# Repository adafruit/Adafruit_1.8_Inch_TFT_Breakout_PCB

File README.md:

# 1.8" Color TFT LCD display with MicroSD Card Breakout

<a href="http://www.adafruit.com/products/358"><br/>Click here to purchase one from the Adafruit shop</a>

This lovely little display breakout is the best way to add a small, colorful and bright display to any project. Since the display uses 4-wire SPI to communicate and has its own pixel-addressable frame buffer, it can be used with every kind of microcontroller. Even a very small one with low memory and few pins available!

The 1.8" display has 128x160 color pixels. Unlike the low cost "Nokia 6110" and similar LCD displays, which are CSTN type and thus have poor color and slow refresh, this display is a true TFT! The TFT driver (ST7735R) can display full 18-bit color (262,144 shades!). And the LCD will always come with the same driver chip so there's no worries that your code will not work from one to the other.

The breakout has the TFT display soldered on (it uses a delicate flex-circuit connector) as well as a ultra-low-dropout 3.3V regulator and a 3/5V level shifter so you can use it with 3.3V or 5V power and logic. We also had a little space so we placed a microSD card holder so you can easily load full color bitmaps from a FAT16/FAT32 formatted microSD card. The microSD card is not included, [but you can pick one up here](https://www.adafruit.com/product/102).

Of course, we wouldn't just leave you with a datasheet and a "good luck!" - [we've written a full open source graphics library that can draw pixels, lines, rectangles, circles, text and bitmaps as well as example code and a wiring tutorial](https://learn.adafruit.com/1-8-tft-display). The code is written for Arduino but can be easily ported to your favorite microcontroller!

### License

Adafruit invests time and resources providing this open source design, please support Adafruit and open-source hardware by purchasing products from [Adafruit](https://www.adafruit.com)!

Designed by Limor Fried/Ladyada for Adafruit Industries.

Creative Commons Attribution/Share-Alike, all text above must be included in any redistribution. See license.txt for additional details.

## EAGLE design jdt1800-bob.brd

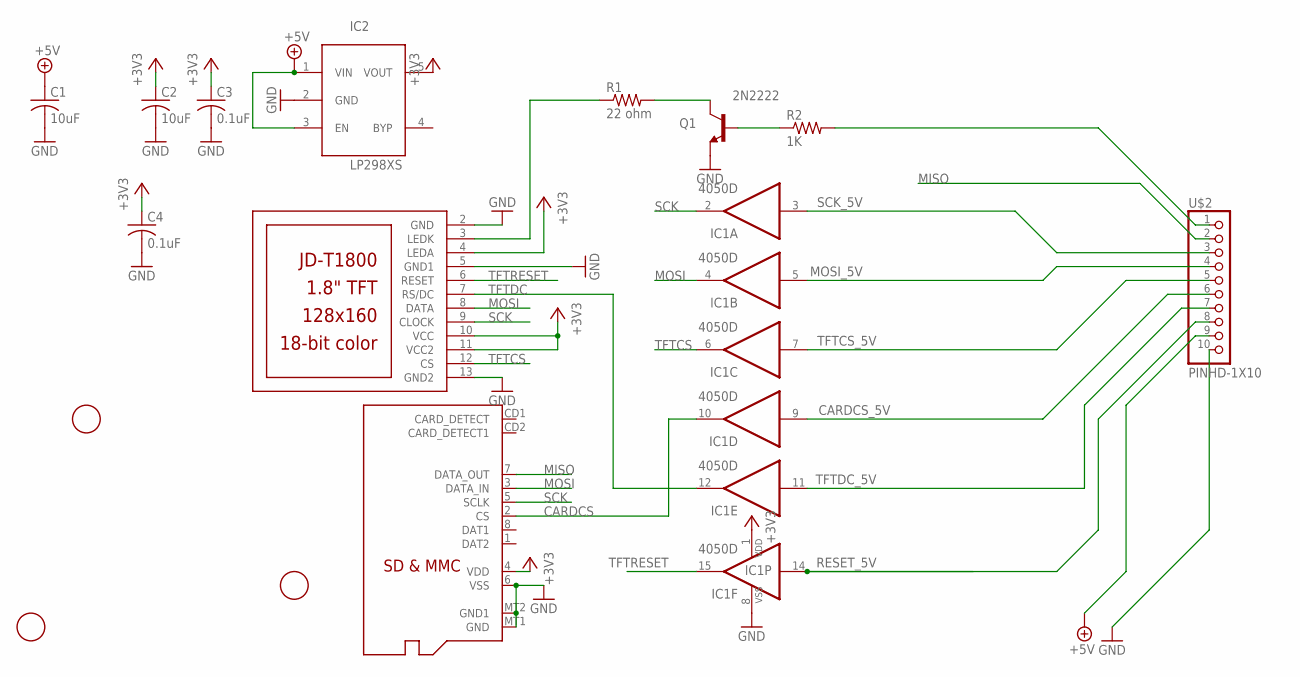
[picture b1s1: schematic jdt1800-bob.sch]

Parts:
C1, C2: 10uF; C0805K
C3, C4: 0.1uF; C0805K
IC1: 4050D; SO16
IC2: LP298XS; SOT23-5L
Q1: 2N2222; SOT23-BEC
Q2: MICROSD
R1: 22 ohm; R0805
R2: 1K; R0805
U$1: JD-T1800
U$2: PINHD-1X10; 1X10-BIG
U$3, U$4, U$5: FIDUCIAL; FIDUCIAL_1MM

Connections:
+3V3: C2.1, C3.1, C4.1, IC1.1 (VDD), IC2.5 (VOUT), Q2.4 (VDD), U$1.4 (LEDA), U$1.10 (VCC), U$1.11 (VCC2)
+5V: C1.1, IC2.1 (VIN), IC2.3 (EN), U$2.9
CARDCS: IC1.10 (O), Q2.2 (CS)
CARDCS_5V: IC1.9 (I), U$2.6
GND: C1.2, C2.2, C3.2, C4.2, IC1.8 (VSS), IC2.2 (GND), Q1.E, Q2.6 (VSS), Q2.MT1 (GND), Q2.MT2 (GND1), U$1.2 (GND), U$1.5 (GND1), U$1.13 (GND2), U$2.10
MISO: Q2.7 (DATA_OUT), U$2.2
MOSI: IC1.4 (O), Q2.3 (DATA_IN), U$1.8 (DATA)
MOSI_5V: IC1.5 (I), U$2.4
unnamed: Q1.B, R2.1
unnamed: R1.1, U$1.3 (LEDK)
unnamed: Q1.C, R1.2
unnamed: R2.2, U$2.1
RESET_5V: IC1.14 (I), U$2.8
SCK: IC1.2 (O), Q2.5 (SCLK), U$1.9 (CLOCK)
SCK_5V: IC1.3 (I), U$2.3
TFTCS: IC1.6 (O), U$1.12 (CS)
TFTCS_5V: IC1.7 (I), U$2.5
TFTDC: IC1.12 (O), U$1.7 (RS/DC)
TFTDC_5V: IC1.11 (I), U$2.7
TFTRESET: IC1.15 (O), U$1.6 (RESET)

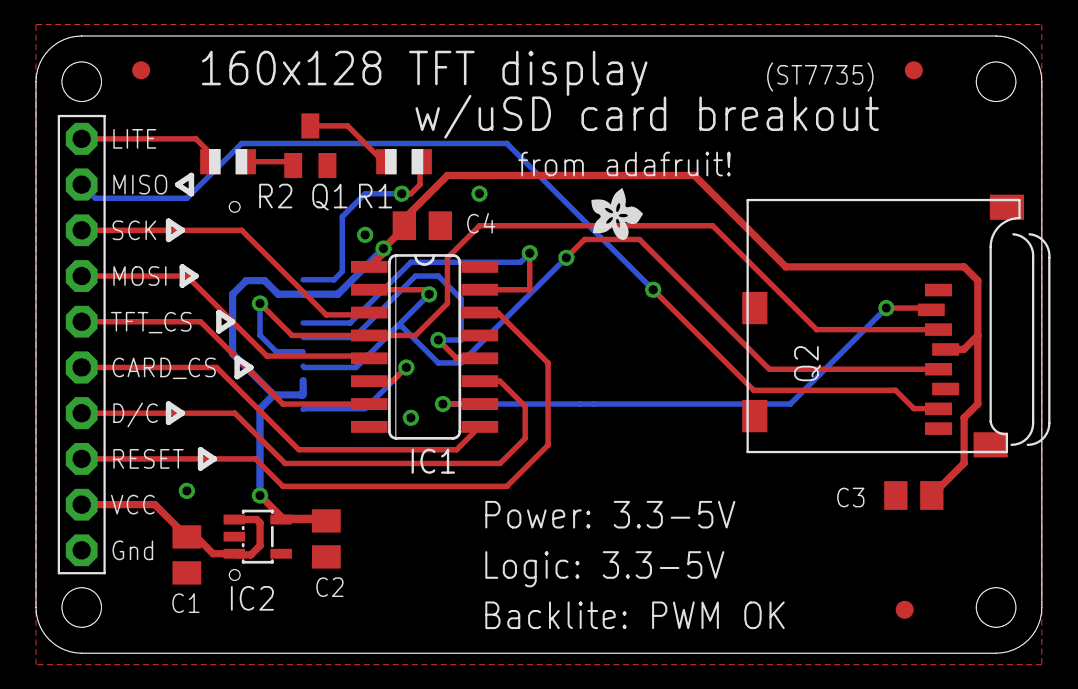
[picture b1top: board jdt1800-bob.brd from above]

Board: 2 copper layers, 55.9 x 34.3 mm, 16 parts (1 on the bottom side), 20 nets.

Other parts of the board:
U$6: ADAFRUIT200MIL

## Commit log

2011-05-30 eaglecad files
2011-05-30 png schem
2019-03-15 image + readme
2026-06-03 update file format to XML
